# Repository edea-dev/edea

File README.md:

# edea python libary and tool

This is the edea commandline tool and kicad parser python library.

## Running the tool

To run the tool for test & development purposes either enter a venv or use poetry to run it:

```sh
# when outside the poetry environment, just run
poetry run python -m edea
# or
poetry shell
# now we're inside the venv and can run
python -m edea
```

## Running the tests

The tests should run in the venv to make sure the development tools are there:

```sh
# outside the poetry environment:
poetry run pytest
# or
poetry shell
# now we're inside the venv and can run like before, but now with test coverage
pytest --cov-report term-missing --cov=edea

# it's also possible to run a single test or a test class
pytest -k TestMetadata
```

### Long running test

`test_parse_all` parses a lot of KiCad 6 files which can take a long time. It
doesn't run by default if the files are not there but you can enable it by
getting them.

```sh
# the files are in the kicad6-test-files git submodule
git submodule update --init
# we'd like to parallelize the tests using pytest-xdist to speed things up
poetry shell
pip install pytest-xdist
# run the tests, automatically detecting the optimal number of processes for your machine
pytest -n auto
```

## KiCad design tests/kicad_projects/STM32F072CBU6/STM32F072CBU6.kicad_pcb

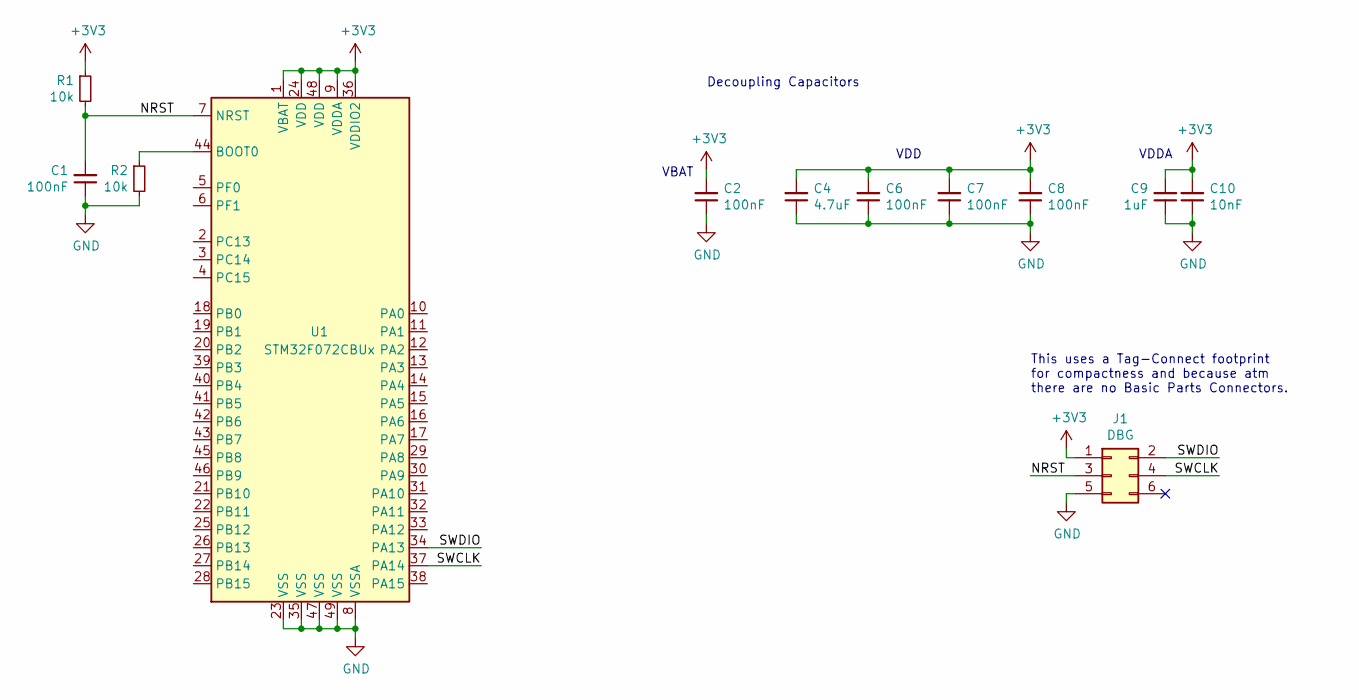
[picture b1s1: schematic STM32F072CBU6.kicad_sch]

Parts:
C1, C2, C6, C7, C8: 100nF; C_0402_1005Metric; JLC 0402
C4: 4.7uF; C_0402_1005Metric; JLC 0402
C9: 1uF; C_0402_1005Metric; JLC 0402
C10: 10nF; C_0402_1005Metric; JLC 0402
J1: DBG; Tag-Connect_TC2030-IDC-NL_2x03_P1.27mm_Vertical; MPN DNP
R1, R2: 10k; R_0402_1005Metric; JLC 0402
U1: STM32F072CBUx; QFN-48-1EP_7x7mm_P0.5mm_EP5.6x5.6mm; JLC UFQFPN-48_EP_7.0x7.0x0.5P

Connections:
+3V3: C2.2, C4.2, C6.2, C7.2, C8.2, C9.2, C10.2, J1.1, R1.1, U1.1 (VBAT), U1.9 (VDDA), U1.24 (VDD), U1.36 (VDDIO2), U1.48 (VDD)
/NRST: C1.2, J1.3, R1.2, U1.7 (NRST)
/SWCLK: J1.4, U1.37 (PA14)
/SWDIO: J1.2, U1.34 (PA13)
GND: C1.1, C2.1, C4.1, C6.1, C7.1, C8.1, C9.1, C10.1, J1.5, R2.2, U1.8 (VSSA), U1.23 (VSS), U1.35 (VSS), U1.47 (VSS), U1.49 (VSS)
unnamed: R2.1, U1.44 (BOOT0)

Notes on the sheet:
VDDA
VBAT
VDD
Decoupling Capacitors
This uses a Tag-Connect footprint for compactness and because atm there are no Basic Parts Connectors.

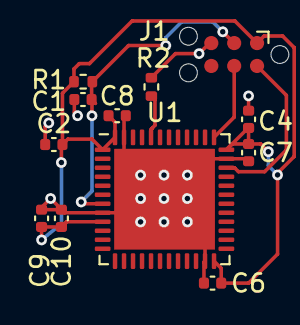
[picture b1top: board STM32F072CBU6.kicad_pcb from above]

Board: 2 copper layers, 12 parts (0 on the bottom side), 6 nets.

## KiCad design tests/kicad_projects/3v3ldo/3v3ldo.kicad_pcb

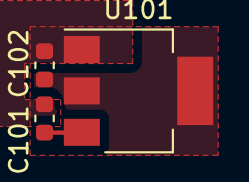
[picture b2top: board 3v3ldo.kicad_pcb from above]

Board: 2 copper layers, 3 parts (0 on the bottom side), 3 nets.

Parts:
C101, C102: 1uF; C_0603_1608Metric
U101: NCP1117-3.3_SOT223; SOT-223-3_TabPin2

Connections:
/GND: C101.2, C102.2, U101.1
/VIN: C101.1, U101.3
/VOUT: C102.1, U101.2

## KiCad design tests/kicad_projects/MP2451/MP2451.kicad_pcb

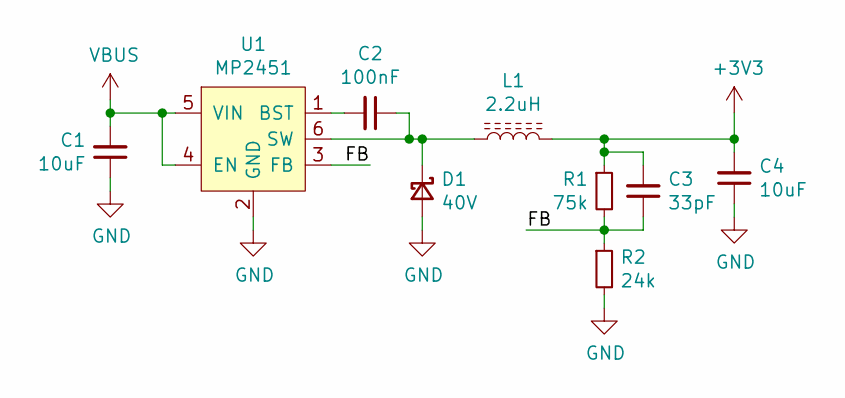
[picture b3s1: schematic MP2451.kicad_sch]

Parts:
C1: 10uF; C_1206_3216Metric; JLC 1206
C2: 100nF; C_0402_1005Metric; JLC 0402
C3: 33pF; C_0402_1005Metric; JLC 0402
C4: 10uF; C_0402_1005Metric; JLC 0402
D1: 40V; D_SOD-123; MPN B5819W; JLC SOD-123
L1: 2.2uH; L_1008_2520Metric; MPN BDCD002520122R2MS1; JLC SMD_2.5x2.0x1.2mm
R1: 75k; R_0402_1005Metric; JLC 0402
R2: 24k; R_0402_1005Metric; JLC 0402
U1: MP2451; SOT-23-6; JLC SOT-23-6L

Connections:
+3V3: C3.2, C4.2, L1.2, R1.1
/FB: C3.1, R1.2, R2.1, U1.3 (FB)
GND: C1.1, C4.1, D1.2 (A), R2.2, U1.2 (GND)
unnamed: C2.1, D1.1 (K), L1.1, U1.6 (SW)
unnamed: C2.2, U1.1 (BST)
VBUS: C1.2, U1.4 (EN), U1.5 (VIN)

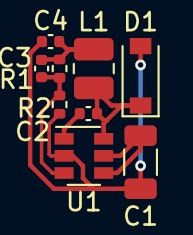
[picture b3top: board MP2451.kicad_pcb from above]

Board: 2 copper layers, 9 parts (0 on the bottom side), 6 nets.

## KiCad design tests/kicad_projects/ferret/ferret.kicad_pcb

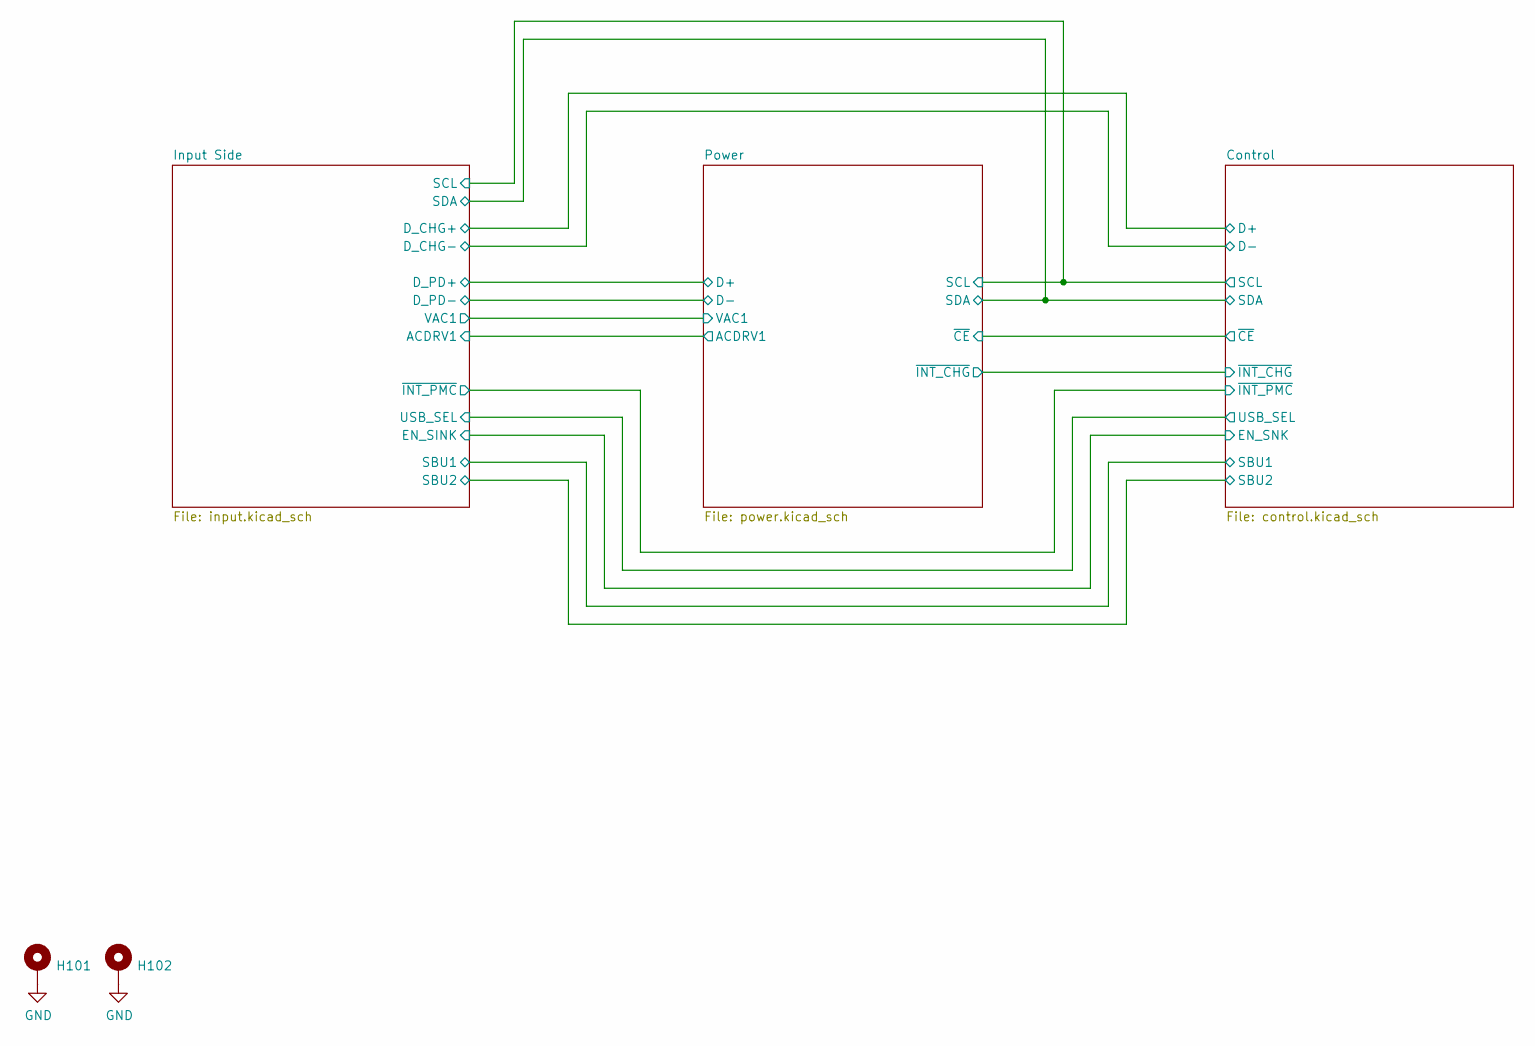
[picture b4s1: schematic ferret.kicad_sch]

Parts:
H101, H102: MountingHole_Pad; MountingHole_3.2mm_M3_ISO14580_Pad; MPN DNP

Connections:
GND: H101.1, H102.1; also elsewhere on the board

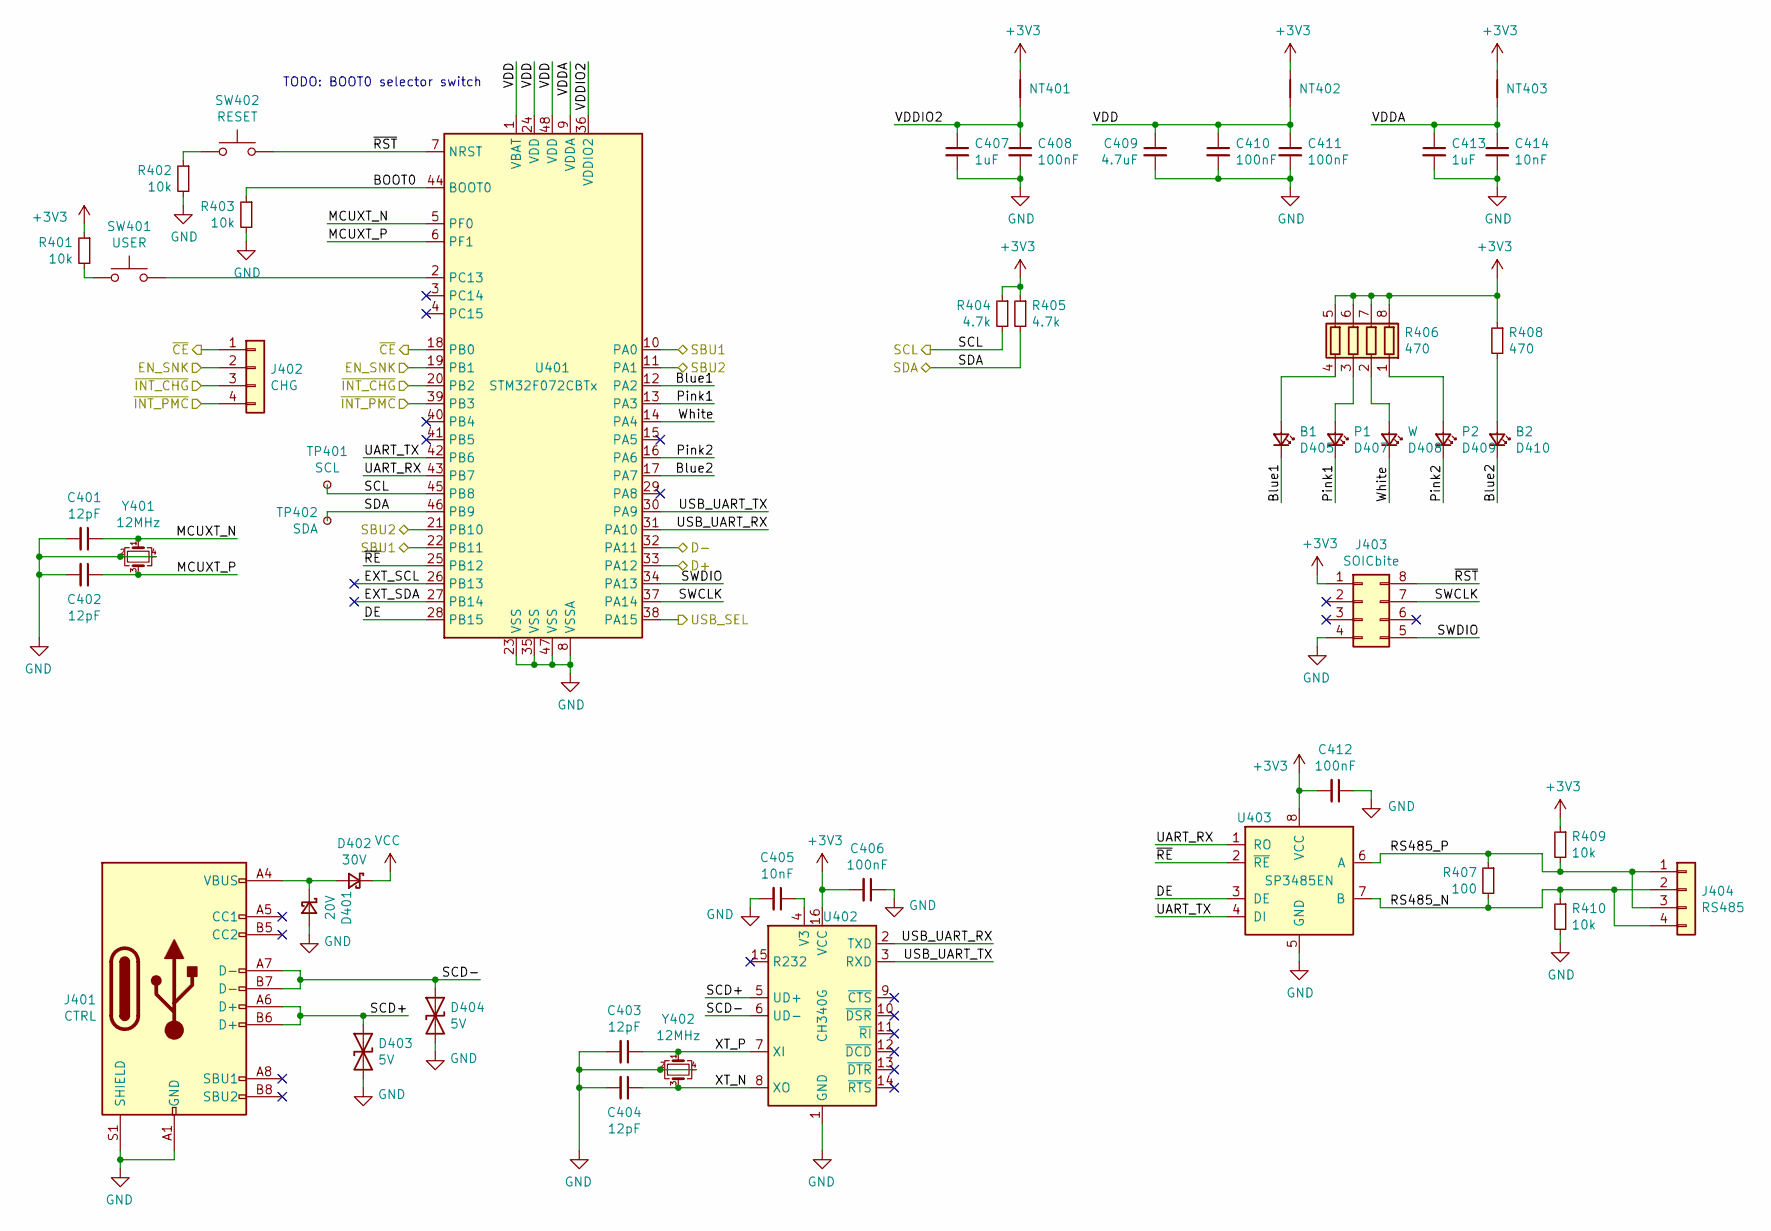
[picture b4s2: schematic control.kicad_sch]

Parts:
C401, C402, C403, C404: 12pF; C_0402_1005Metric; MPN 0402CG120J500NT; LCSC C1547
C405, C414: 10nF; C_0402_1005Metric; LCSC C15195
C406, C408, C410, C411, C412: 100nF; C_0402_1005Metric; MPN CL05B104KO5NNNC; JLC 0402
C407, C413: 1uF; C_0402_1005Metric; LCSC C52923
C409: 4.7uF; C_0603_1608Metric; MPN CL10A475KO8NNNC; JLC 0603
D401: 20V; D_SOD-123; MPN B5819W; LCSC C8598
D402: 30V; D_SOD-123; MPN B5819W; LCSC C8598
D403, D404: 5V; D_SOD-523; MPN ESD5Z3.3T1G; JLC SOD-523
D405: B1; LED_0603_1608Metric_Castellated; MPN OSB60603C1E
D407: P1; LED_0603_1608Metric_Castellated; MPN OSK40603C1E
D408: W; LED_0603_1608Metric_Castellated; MPN OSW50603C1E
D409: P2; LED_0603_1608Metric_Castellated; MPN OSK40603C1E
D410: B2; LED_0603_1608Metric_Castellated; MPN OSB60603C1E
J401: CTRL; USB_C_Receptacle_XKB_U262-16XN-4BVC11
J402: CHG; PinHeader_1x04_P2.54mm_Vertical
J403: SOICbite; SOIC_clipProgSmall
J404: RS485; PinHeader_1x04_P2.54mm_Vertical
NT401: VDDIO2; NetTie-2_SMD_Pad0.5mm; MPN DNP
NT402: VDD; NetTie-2_SMD_Pad0.5mm; MPN DNP
NT403: VDDA; NetTie-2_SMD_Pad0.5mm; MPN DNP
R401, R402, R403, R409, R410: 10k; R_0603_1608Metric; JLC 0603
R404, R405: 4.7k; R_0603_1608Metric; JLC 0603
R406: 470; R_Array_Convex_4x0603; MPN 4D03WGJ0471T5E; JLC 0603_x4
R407: 100; R_0603_1608Metric; MPN 0603WAF1000T5E; JLC 0603
R408: 470; R_0603_1608Metric; JLC 0603
SW401: USER; SW_SPST_PTS636_G
SW402: RESET; SW_SPST_PTS636_G
TP401: SCL; TestPoint_THTPad_D2.0mm_Drill1.0mm
TP402: SDA; TestPoint_THTPad_D2.0mm_Drill1.0mm
U401: STM32F072CBTx; LQFP-48_7x7mm_P0.5mm; MPN STM32F072C8T6; JLC LQFP-48_7.0x7.0x0.5P
U402: CH340G; SOIC-16_3.9x9.9mm_P1.27mm; MPN CH340G; JLC SOIC-16_3.9x9.9x1.27P
U403: SP3485EN; SOIC-8_3.9x4.9mm_P1.27mm; MPN SP3485EN-L/TR; JLC SOIC-8_3.9x4.9x1.27P
Y401, Y402: 12MHz; Crystal_SMD_3225-4Pin_3.2x2.5mm; MPN X322512MSB4SI; JLC SMD-3225_4P

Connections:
+3V3: C406.2, C412.2, J403.1, NT401.1, NT402.1, NT403.1, R401.1, R404.1, R405.1, R406.5 (R4.2), R406.6 (R3.2), R406.7 (R2.2), R406.8 (R1.2), R408.1, R409.1, U402.16 (VCC), U403.8 (VCC); also elsewhere on the board
/Control/BOOT0: R403.1, U401.44 (BOOT0)
/Control/Blue1: D405.1 (K), U401.12 (PA2)
/Control/Blue2: D410.1 (K), U401.17 (PA7)
/Control/D+: U401.33 (PA12); also elsewhere on the board
/Control/D-: U401.32 (PA11); also elsewhere on the board
/Control/DE: U401.28 (PB15), U403.3 (DE)
/Control/EXT_SCL: U401.26 (PB13)
/Control/EXT_SDA: U401.27 (PB14)
/Control/MCUXT_N: C401.1, U401.5 (PF0), Y401.1
/Control/MCUXT_P: C402.1, U401.6 (PF1), Y401.3
/Control/Pink1: D407.1 (K), U401.13 (PA3)
/Control/Pink2: D409.1 (K), U401.16 (PA6)
/Control/RS485_N: J404.2, J404.4, R407.2, R410.1, U403.7 (B)
/Control/RS485_P: J404.1, J404.3, R407.1, R409.2, U403.6 (A)
/Control/SBU1: U401.10 (PA0), U401.22 (PB11); also elsewhere on the board
/Control/SBU2: U401.11 (PA1), U401.21 (PB10); also elsewhere on the board
/Control/SCD+: D403.1 (A1), J401.A6 (D+), J401.B6 (D+), U402.5 (UD+)
/Control/SCD-: D404.1 (A1), J401.A7 (D-), J401.B7 (D-), U402.6 (UD-)
/Control/SCL: R404.2, TP401.1, U401.45 (PB8); also elsewhere on the board
/Control/SDA: R405.2, TP402.1, U401.46 (PB9); also elsewhere on the board
/Control/SWCLK: J403.7, U401.37 (PA14)
/Control/SWDIO: J403.5, U401.34 (PA13)
/Control/UART_RX: U401.43 (PB7), U403.1 (RO)
/Control/UART_TX: U401.42 (PB6), U403.4 (DI)
/Control/USB_SEL: U401.38 (PA15); also elsewhere on the board
/Control/USB_UART_RX: U401.31 (PA10), U402.2 (TXD)
/Control/USB_UART_TX: U401.30 (PA9), U402.3 (RXD)
/Control/VDD: C409.1, C410.1, C411.1, NT402.2, U401.1 (VBAT), U401.24 (VDD), U401.48 (VDD)
/Control/VDDA: C413.1, C414.1, NT403.2, U401.9 (VDDA)
/Control/VDDIO2: C407.1, C408.1, NT401.2, U401.36 (VDDIO2)
/Control/White: D408.1 (K), U401.14 (PA4)
/Control/XT_N: C404.1, U402.8 (XO), Y402.3
/Control/XT_P: C403.1, U402.7 (XI), Y402.1
/Control/~CE: J402.1, U401.18 (PB0); also elsewhere on the board
/Control/~INT_CHG: J402.3, U401.20 (PB2); also elsewhere on the board
/Control/~INT_PMC: J402.4, U401.39 (PB3); also elsewhere on the board
/Control/~RE: U401.25 (PB12), U403.2 (~RE)
/Control/~RST: J403.8, SW402.2, U401.7 (NRST)
/Input Side/EN_SINK: J402.2, U401.19 (PB1); also elsewhere on the board
GND: C401.2, C402.2, C403.2, C404.2, C405.2, C406.1, C407.2, C408.2, C409.2, C410.2, C411.2, C412.1, C413.2, C414.2, D401.2 (A), D403.2 (A2), D404.2 (A2), J401.A1 (GND), J401.A12 (GND), J401.B1 (GND), J401.B12 (GND), J401.S1 (SHIELD), J403.4, R402.2, R403.2, R410.2, U401.8 (VSSA), U401.23 (VSS), U401.35 (VSS), U401.47 (VSS), U402.1 (GND), U403.5 (GND), Y401.2, Y401.4, Y402.2, Y402.4; also elsewhere on the board
unnamed: C405.1, U402.4 (V3)
unnamed: D401.1 (K), D402.2 (A), J401.A4 (VBUS), J401.A9 (VBUS), J401.B4 (VBUS), J401.B9 (VBUS)
unnamed: D405.2 (A), R406.4 (R4.1)
unnamed: D407.2 (A), R406.3 (R3.1)
unnamed: D408.2 (A), R406.2 (R2.1)
unnamed: D409.2 (A), R406.1 (R1.1)
unnamed: D410.2 (A), R408.2
unnamed: R401.2, SW401.1
unnamed: R402.1, SW402.1
unnamed: SW401.2, U401.2 (PC13)
VCC: D402.1 (K); also elsewhere on the board

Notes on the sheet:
TODO: BOOT0 selector switch

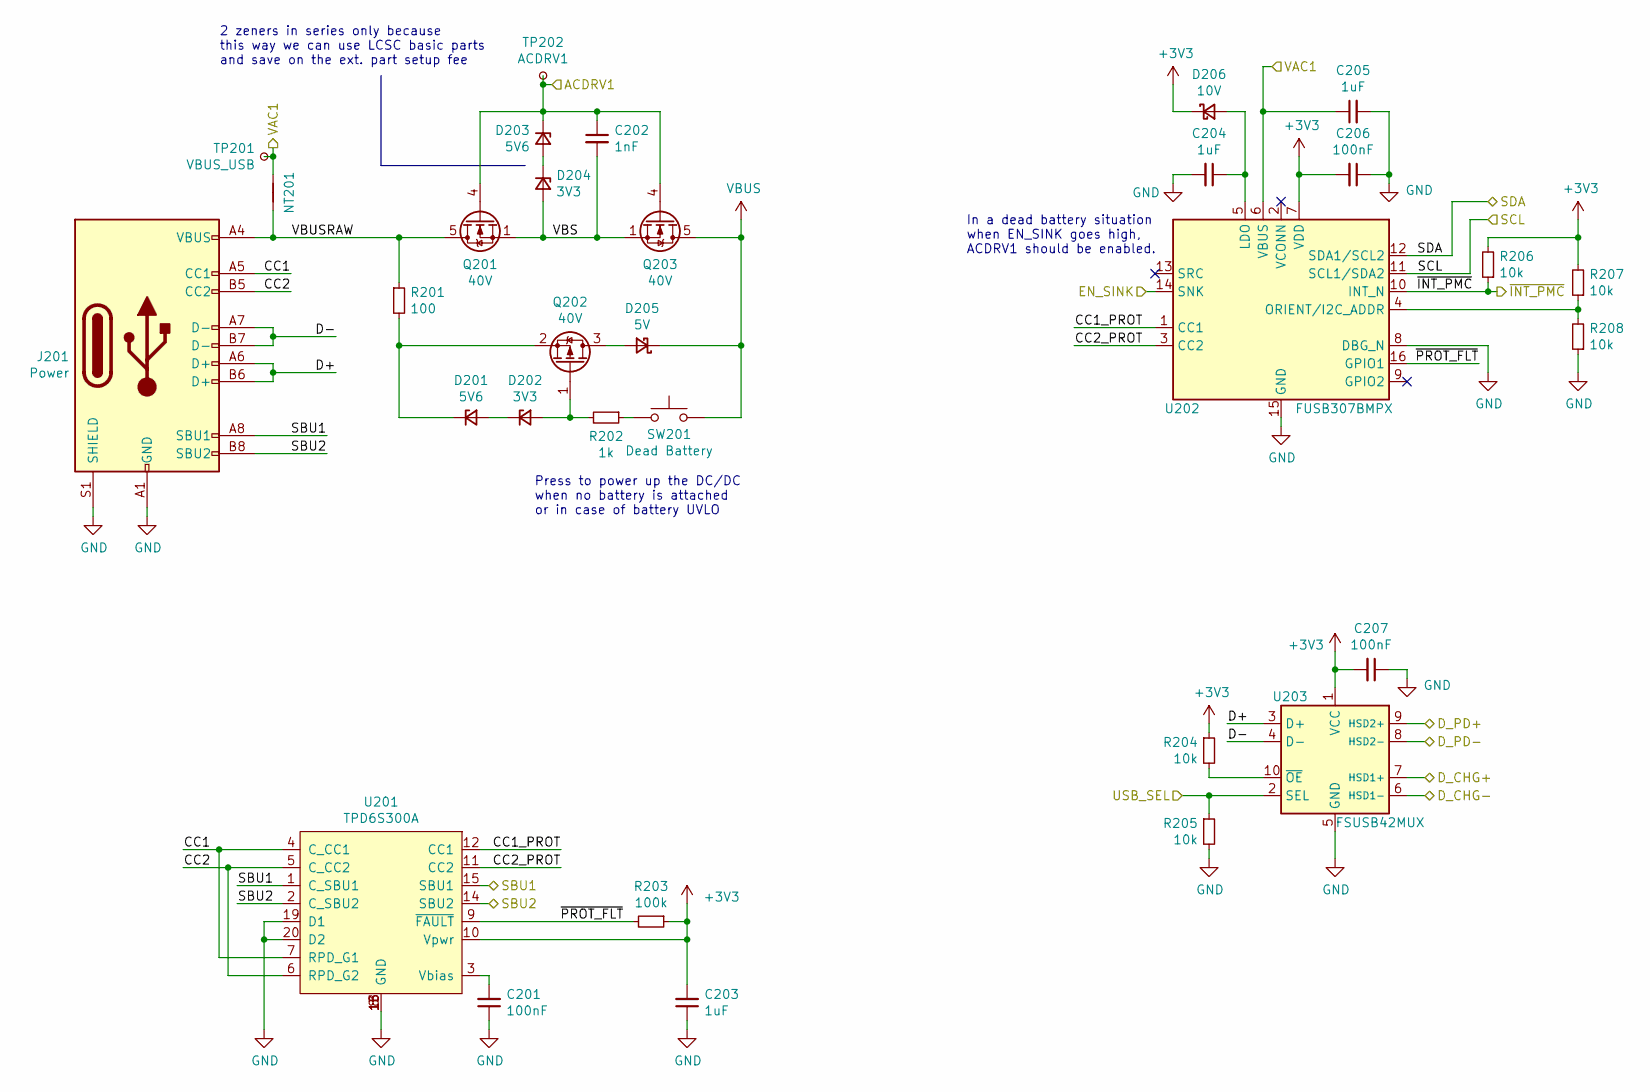
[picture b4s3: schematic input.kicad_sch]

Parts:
C201, C206: 100nF; C_0603_1608Metric; MPN CC0603KRX7R9BB104; JLC 0603
C202: 1nF; C_0402_1005Metric; JLC 0402
C203: 1uF; C_0603_1608Metric; MPN CL10A105KB8NNNC; LCSC C15849
C204: 1uF; C_0603_1608Metric
C205: 1uF; C_0603_1608Metric; LCSC C15849
C207: 100nF; C_0402_1005Metric; JLC 0402
D201, D203: 5V6; D_MiniMELF; MPN ZMM5V6; JLC LL-34
D202, D204: 3V3; D_MiniMELF; MPN ZMM3V3; JLC LL-34
D205: 5V; D_SOD-123; MPN B5819W; JLC SOD-123
D206: 10V; D_SOD-123; MPN B5819W; LCSC C8598
J201: Power; USB_C_Receptacle_XKB_U262-16XN-4BVC11
NT201: UwU; NetTie-2_SMD_Pad0.5mm; MPN DNP
Q201, Q203: 40V; Vishay_PowerPAK_1212-8_Single; MPN SiSS10ADN
Q202: 40V; SOT-23; MPN AO3401; JLC SOT-23-3L
R201: 100; R_1206_3216Metric; MPN 1206W4F1000T5E; JLC 1206
R202: 1k; R_0603_1608Metric; MPN 0603WAF1001T5E; JLC 0603
R203: 100k; R_0402_1005Metric; JLC 0402
R204, R205: 10k; R_0603_1608Metric; JLC 0603
R206: 10k; R_0402_1005Metric; JLC 0402
R207, R208: 10k; R_0603_1608Metric; MPN DNP; JLC 0603
SW201: Dead Battery; SW_SPST_PTS636_G
TP201: VBUS_USB; TestPoint_THTPad_D2.0mm_Drill1.0mm
TP202: ACDRV1; TestPoint_THTPad_D2.0mm_Drill1.0mm
U201: TPD6S300A; QFN-20-1EP_3x3mm_P0.4mm_EP1.65x1.65mm; MPN TPD6S300ARUKR
U202: FUSB307BMPX; WQFN-16-1EP_3x3mm_P0.5mm_EP1.75x1.75mm
U203: FSUSB42MUX; MSOP-10_3x3mm_P0.5mm; MPN FSUSB42MUX; JLC MSOP-10_3.0x3.0x0.5P

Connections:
+3V3: C203.2, C206.2, C207.2, D206.1 (K), R203.1, R204.1, R206.2, R207.2, U201.10 (Vpwr), U202.7 (VDD), U203.1 (VCC); also elsewhere on the board
/Control/D+: U203.7 (HSD1+); also elsewhere on the board
/Control/D-: U203.6 (HSD1-); also elsewhere on the board
/Control/SBU1: J201.A8 (SBU1), U201.1 (C_SBU1), U201.15 (SBU1); also elsewhere on the board
/Control/SBU2: J201.B8 (SBU2), U201.2 (C_SBU2), U201.14 (SBU2); also elsewhere on the board
/Control/SCL: U202.11 (SCL1/SDA2); also elsewhere on the board
/Control/SDA: U202.12 (SDA1/SCL2); also elsewhere on the board
/Control/USB_SEL: R205.1, U203.2 (SEL); also elsewhere on the board
/Control/~INT_PMC: R206.1, U202.10 (INT_N); also elsewhere on the board
/Input Side/ACDRV1: C202.1, D203.1 (K), Q201.4 (G), Q203.4 (G), TP202.1; also elsewhere on the board
/Input Side/CC1: J201.A5 (CC1), U201.4 (C_CC1), U201.7 (RPD_G1)
/Input Side/CC1_PROT: U201.12 (CC1), U202.1 (CC1)
/Input Side/CC2: J201.B5 (CC2), U201.5 (C_CC2), U201.6 (RPD_G2)
/Input Side/CC2_PROT: U201.11 (CC2), U202.3 (CC2)
/Input Side/D+: J201.A6 (D+), J201.B6 (D+), U203.3 (D+)
/Input Side/D-: J201.A7 (D-), J201.B7 (D-), U203.4 (D-)
/Input Side/EN_SINK: U202.14 (SNK); also elsewhere on the board
/Input Side/VAC1: C205.1, NT201.1, TP201.1, U202.6 (VBUS); also elsewhere on the board
/Input Side/VBS: C202.2, D204.2 (A), Q201.1 (S), Q201.2 (S), Q201.3 (S), Q203.1 (S), Q203.2 (S), Q203.3 (S)
/Input Side/VBUSRAW: J201.A4 (VBUS), J201.A9 (VBUS), J201.B4 (VBUS), J201.B9 (VBUS), NT201.2, Q201.5 (D), R201.1
/Input Side/~PROT_FLT: R203.2, U201.9 (~FAULT), U202.16 (GPIO1)
/Power/D+: U203.9 (HSD2+); also elsewhere on the board
/Power/D-: U203.8 (HSD2-); also elsewhere on the board
GND: C201.1, C203.1, C204.2, C205.2, C206.1, C207.1, J201.A1 (GND), J201.A12 (GND), J201.B1 (GND), J201.B12 (GND), J201.S1 (SHIELD), R205.2, R208.1, U201.8 (GND), U201.13 (GND), U201.16 (NC), U201.17 (NC), U201.18 (GND), U201.19 (D1), U201.20 (D2), U201.21 (Thermal_Pad), U202.8 (DBG_N), U202.15 (GND), U202.17 (GND), U203.5 (GND); also elsewhere on the board
unnamed: C201.2, U201.3 (Vbias)
unnamed: C204.1, D206.2 (A), U202.5 (LDO)
unnamed: D201.1 (K), Q202.2 (S), R201.2
unnamed: D201.2 (A), D202.1 (K)
unnamed: D202.2 (A), Q202.1 (G), R202.2
unnamed: D203.2 (A), D204.1 (K)
unnamed: D205.2 (A), Q202.3 (D)
unnamed: R202.1, SW201.1
unnamed: R204.2, U203.10 (~OE)
unnamed: R207.1, R208.2, U202.4 (ORIENT/I2C_ADDR)
VBUS: D205.1 (K), Q203.5 (D), SW201.2; also elsewhere on the board

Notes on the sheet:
2 zeners in series only because this way we can use LCSC basic parts and save on the ext. part setup fee
In a dead battery situation when EN_SINK goes high, ACDRV1 should be enabled.
Press to power up the DC/DC when no battery is attached or in case of battery UVLO

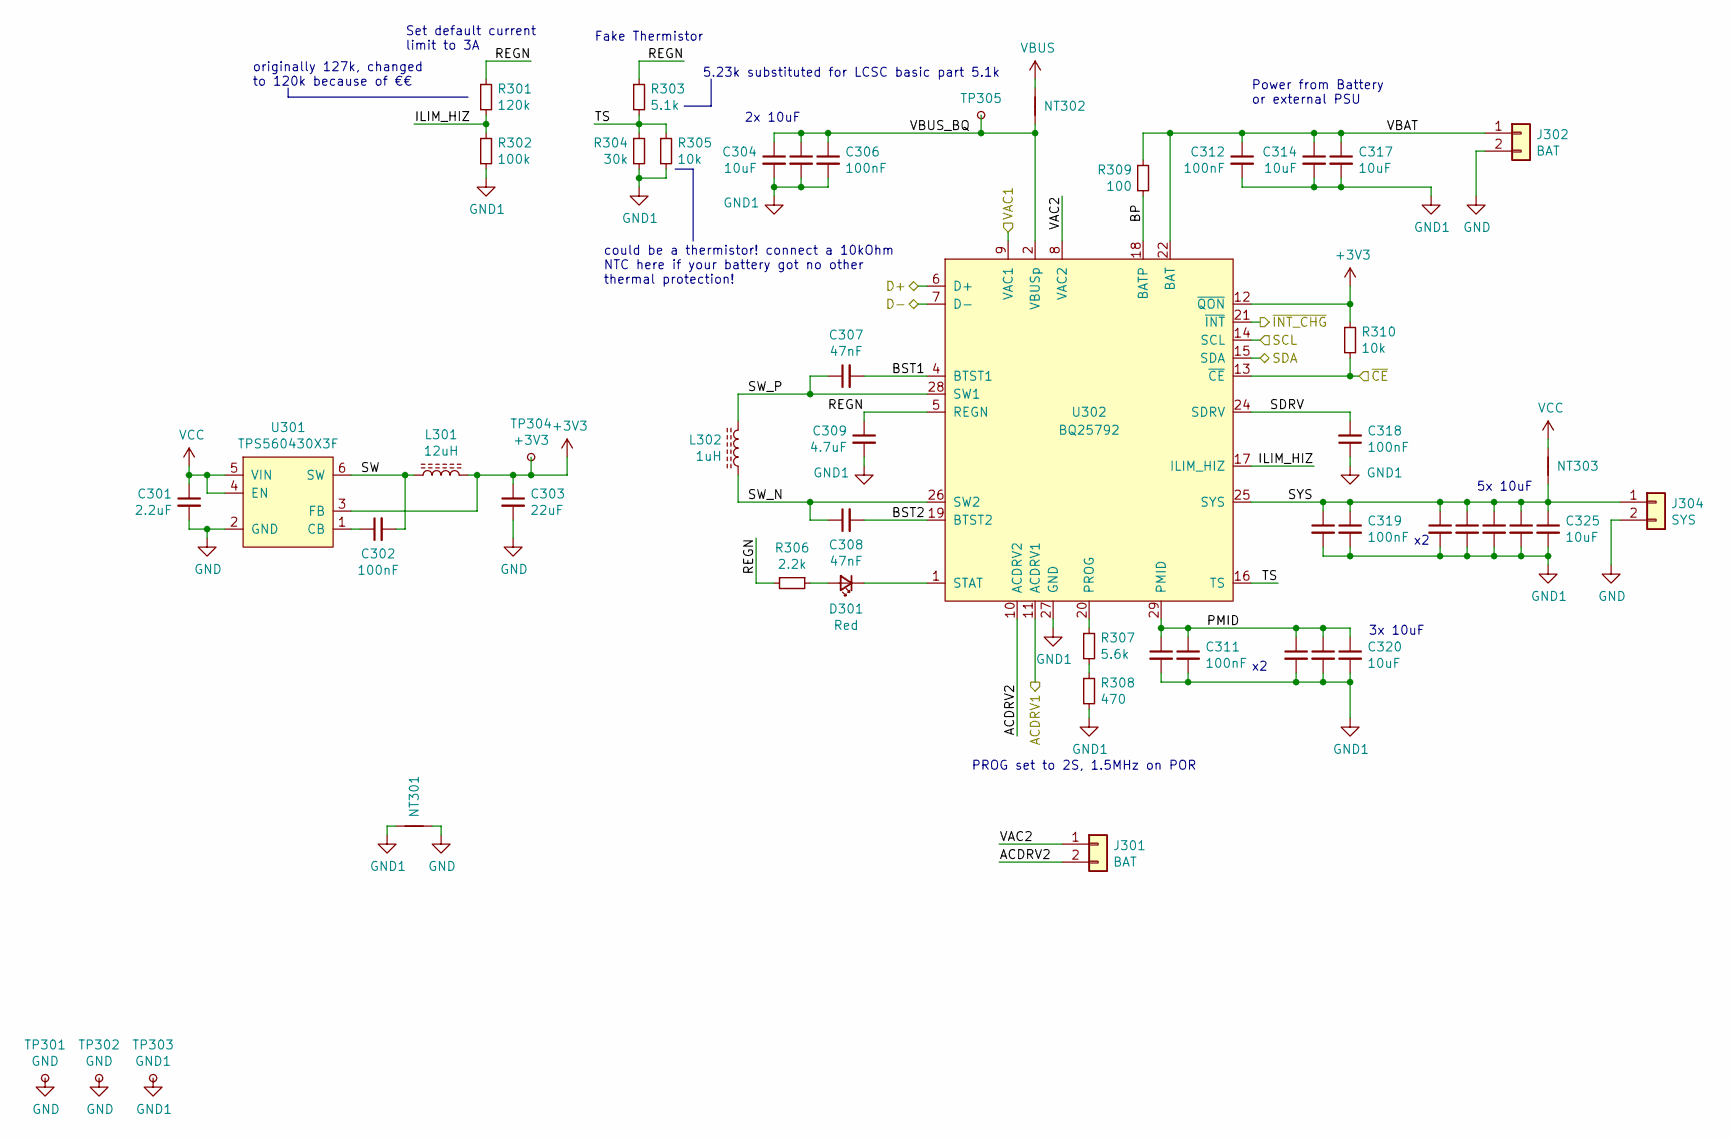
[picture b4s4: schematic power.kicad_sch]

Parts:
C301: 2.2uF; C_0805_2012Metric; MPN 0805F225M500NT; JLC 0805
C302: 100nF; C_0603_1608Metric; MPN CC0603KRX7R9BB104; JLC 0603
C303: 22uF; C_0805_2012Metric; MPN CL21A226MAQNNNE; JLC 0805
C304, C305, C313, C314, C316, C317, C320, C321, C322, C323, C324, C325: 10uF; C_1206_3216Metric; MPN CL31A106KBHNNNE; JLC 1206
C306, C312: 100nF; C_0402_1005Metric; JLC 0402
C307, C308: 47nF; C_0603_1608Metric
C309: 4.7uF; C_0603_1608Metric; MPN CL10A475KO8NNNC; JLC 0603
C310, C311, C315, C319: 100nF; C_0603_1608Metric
C318: 100nF; C_0402_1005Metric
D301: Red; LED_0603_1608Metric_Castellated
J301, J302: BAT; PinSocket_1x02_P2.54mm_Vertical
J304: SYS; PinSocket_1x02_P2.54mm_Vertical
L301: 12uH; L_Bourns_SRN6045TA; MPN SRN6045TA-120M
L302: 1uH; L_Bourns_SRP1245A; MPN SRP1265A-1R0M
NT301: chonk; NetTie-2_SMD_Pad2.0mm
NT302: chonk_vbus; NetTie-2_SMD_Pad2.0mm
NT303: chonk; NetTie-2_SMD_Pad0.5mm
R301: 120k; R_0603_1608Metric; JLC 0603
R302: 100k; R_0603_1608Metric; JLC 0603
R303: 5.1k; R_0603_1608Metric; JLC 0603
R304: 30k; R_0603_1608Metric; LCSC C22984
R305, R310: 10k; R_0603_1608Metric; JLC 0603
R306: 2.2k; R_0603_1608Metric; MPN 0603WAF2201T5E; JLC 0603
R307: 5.6k; R_0402_1005Metric; JLC 0603
R308: 470; R_0402_1005Metric; LCSC C25117
R309: 100; R_0603_1608Metric; MPN 0603WAF1000T5E; JLC 0603
TP301, TP302: GND; TestPoint_THTPad_D2.0mm_Drill1.0mm
TP303: GND1; TestPoint_THTPad_D2.0mm_Drill1.0mm
TP304: +3V3; TestPoint_THTPad_D2.0mm_Drill1.0mm
TP305: VBUS_BQ; TestPoint_THTPad_D2.0mm_Drill1.0mm
U301: TPS560430X3F; SOT-23-6; JLC SOT-23-6L
U302: BQ25792; Texas_VQFN-HR_RQM_4x4mm_P0.40-0.45mm

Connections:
+3V3: C303.1, L301.2, R310.1, TP304.1, U301.3 (FB), U302.12 (~QON); also elsewhere on the board
/Control/SCL: U302.14 (SCL); also elsewhere on the board
/Control/SDA: U302.15 (SDA); also elsewhere on the board
/Control/~CE: R310.2, U302.13 (~CE); also elsewhere on the board
/Control/~INT_CHG: U302.21 (~INT); also elsewhere on the board
/Input Side/ACDRV1: U302.11 (ACDRV1); also elsewhere on the board
/Input Side/VAC1: U302.9 (VAC1); also elsewhere on the board
/Power/ACDRV2: J301.2, U302.10 (ACDRV2)
/Power/BP: R309.2, U302.18 (BATP)
/Power/BST1: C307.2, U302.4 (BTST1)
/Power/BST2: C308.2, U302.19 (BTST2)
/Power/D+: U302.6 (D+); also elsewhere on the board
/Power/D-: U302.7 (D-); also elsewhere on the board
/Power/ILIM_HIZ: R301.2, R302.1, U302.17 (ILIM_HIZ)
/Power/PMID: C310.1, C311.1, C313.1, C316.1, C320.1, U302.29 (PMID)
/Power/REGN: C309.1, R301.1, R303.1, R306.2, U302.5 (REGN)
/Power/SDRV: C318.2, U302.24 (SDRV)
/Power/SW: C302.2, L301.1, U301.6 (SW)
/Power/SW_N: C308.1, L302.1, U302.26 (SW2)
/Power/SW_P: C307.1, L302.2, U302.28 (SW1)
/Power/SYS: C315.1, C319.1, C321.1, C322.1, C323.1, C324.1, C325.1, J304.1, NT303.2, U302.25 (SYS)
/Power/TS: R303.2, R304.1, R305.1, U302.16 (TS)
/Power/VAC2: J301.1, U302.8 (VAC2)
/Power/VBAT: C312.1, C314.1, C317.1, J302.1, R309.1, U302.22 (BAT), U302.23 (BAT)
GND: C301.2, C303.2, J302.2, J304.2, NT301.2, TP301.1, TP302.1, U301.2 (GND); also elsewhere on the board
GND1: C304.2, C305.2, C306.2, C309.2, C310.2, C311.2, C312.2, C313.2, C314.2, C315.2, C316.2, C317.2, C318.1, C319.2, C320.2, C321.2, C322.2, C323.2, C324.2, C325.2, NT301.1, R302.2, R304.2, R305.2, R308.2, TP303.1, U302.27 (GND)
unnamed: C302.1, U301.1 (CB)
unnamed: D301.1 (K), U302.1 (STAT)
unnamed: D301.2 (A), R306.1
unnamed: R307.1, U302.20 (PROG)
unnamed: R307.2, R308.1
VBUS: NT302.1; also elsewhere on the board
VBUSp: C304.1, C305.1, C306.1, NT302.2, TP305.1, U302.2 (VBUSp), U302.3 (VBUSp)
VCC: C301.1, NT303.1, U301.4 (EN), U301.5 (VIN); also elsewhere on the board

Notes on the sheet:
could be a thermistor! connect a 10kOhm NTC here if your battery got no other thermal protection!
2x 10uF
PROG set to 2S, 1.5MHz on POR
originally 127k, changed to 120k because of €€
5x 10uF
Power from Battery or external PSU
Set default current limit to 3A
5.23k substituted for LCSC basic part 5.1k
Fake Thermistor
3x 10uF

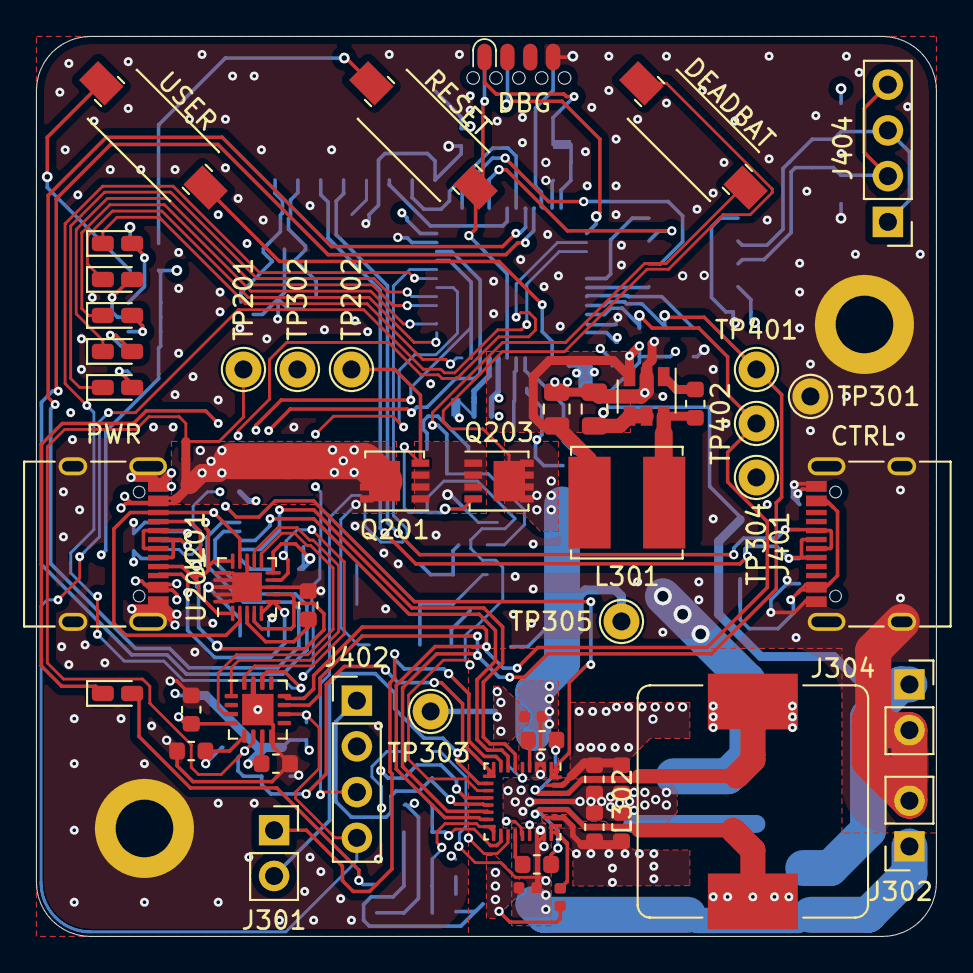
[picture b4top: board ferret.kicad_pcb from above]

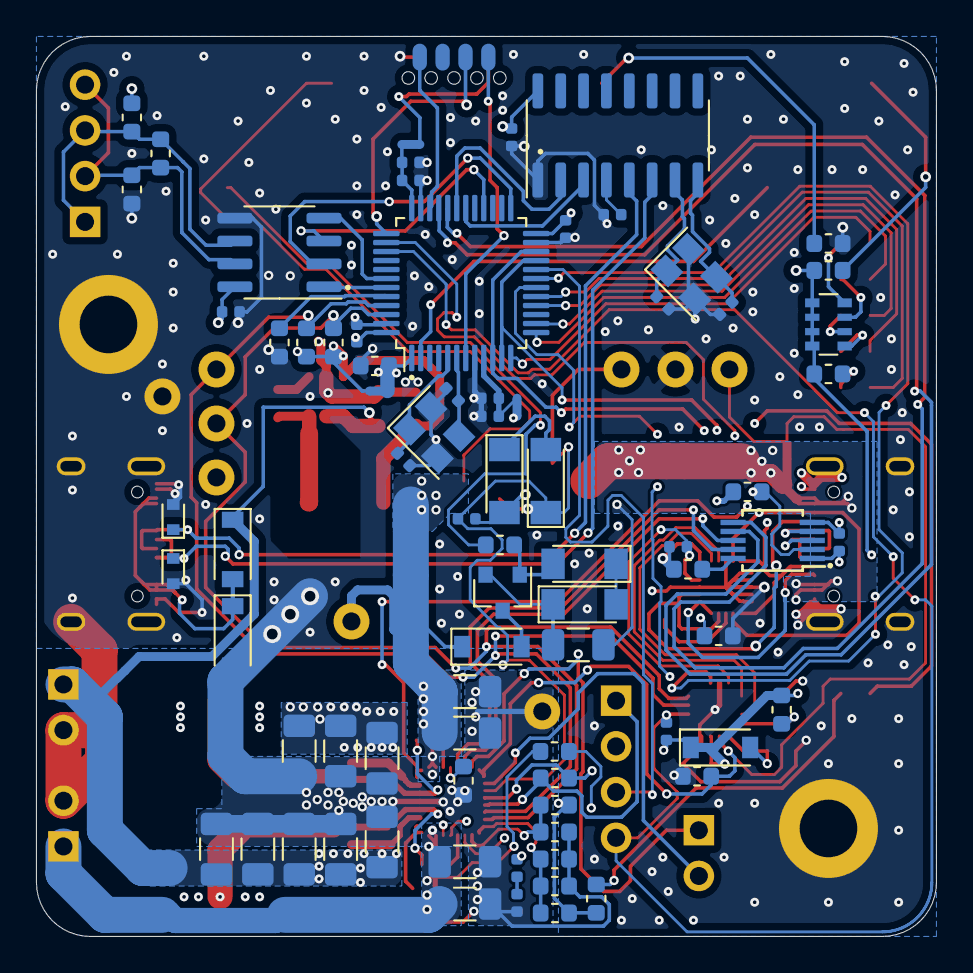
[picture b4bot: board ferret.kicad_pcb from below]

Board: 4 copper layers, 50.0 x 50.0 mm, 134 parts (81 on the bottom side), 96 nets.

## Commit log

2022-03-15 more progress
2022-04-06 schematic merge works now
    still needs better placement logic
2022-05-03 first public push of new edea tooling
2022-05-03 run linter, add pytest as dev dependency
2022-05-03 add gcc for numpy
2022-05-03 use ubuntu image
2022-05-03 fix some pylint stuff, add bandit
2022-05-03 publish package to gitlab registry
2022-05-03 add ferret kicad project as a complex example
    this is for testing the metadata parsing and
    later also rendering of schematics and PCBs.
2022-05-03 cleaned up argument parsing a bit
2022-05-03 Changes by elen
2022-05-03 added conftest.py
2022-05-05 add wip schematic merge
    this needs some test schematics and integration tests
    to be considered stable, but should do the thing.
2022-05-05 add test projects for schematic and pcb merge
2022-05-05 add schematic merge test
2022-05-06 refactor into separate files and add LICENSE.md
2022-05-06 shuffle files around some more
    it should conform with python packaging standards now
2022-05-08 copy merged schematics to output and generate project file
2022-05-08 wrap to next row if there's too many sheets to be placed in the main schematic
2022-05-08 lower numpy version requirement to the latest alpine version
2022-05-12 add basic instructions on how to run the tool
2022-05-12 Add stroke/fill support to draw()
2022-05-12 Add rendering tests
2022-05-13 add example with colors
2022-05-26 benchmark parse time and memory use
    this uses a rather large pcb file as baseline so that we can see
    how the parser performs in a real world situation.
2022-05-26 improve mem test
2022-05-26 gitlab ci runner is really slow
2022-05-26 run tests on github too, remove pyflame dev dep
2022-05-26 corners works now
2022-07-05 pcb bounding boxes work now
2022-07-05 extract more metadata
2022-07-05 moving pcbs works now
2022-07-05 pcb merge works, for some definition of working
2022-07-15 modify paths and randomize tstamp's on merge
2022-07-18 fix some lints, start net-renaming
2022-08-11 fix tokenizer regex
    it didn't like escaped quotes in strings which made the parser fail
2022-08-11 raise an error on pre 6.0 files, other fixes
    * fix sheet file property access
    * fix iterating sub-sheets if there's only one
2022-08-11 global scale is still off, but it's drawing lines!
2022-08-11 figured out the scale factor, formatted
2022-08-12 format + fix draw tests
2022-08-16 Test that parses more than 1500 KiCad projects
2022-08-28 wip for drawing
2022-08-28 fix bounding box not getting calculated
    if some elements were missing it would err out
    when calculating the bounding of a module making
    metadata extraction fail in the process
2022-08-30 format and fix linter issues
2022-08-30 more pylint
2022-09-15 Refactor get_path_to_test_project
2022-09-18 Add Pydantic types
2022-09-18 Enable existing schematic render tests
2022-09-20 Add Image diff functionality
2022-09-20 Add a types.parser module
2022-09-20 use same parameters for diff too
